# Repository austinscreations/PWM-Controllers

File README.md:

# PWM-Controllers

This project has been expanded - tehre are now controlelrs that use a sheild attached to a LilyGO POE, A board using a D1 mini. both of those baords offer 5ch of LED control

Then theres the PWM controller with 16ch expanble i2c module and the room8266 controlelr for controlling said board.

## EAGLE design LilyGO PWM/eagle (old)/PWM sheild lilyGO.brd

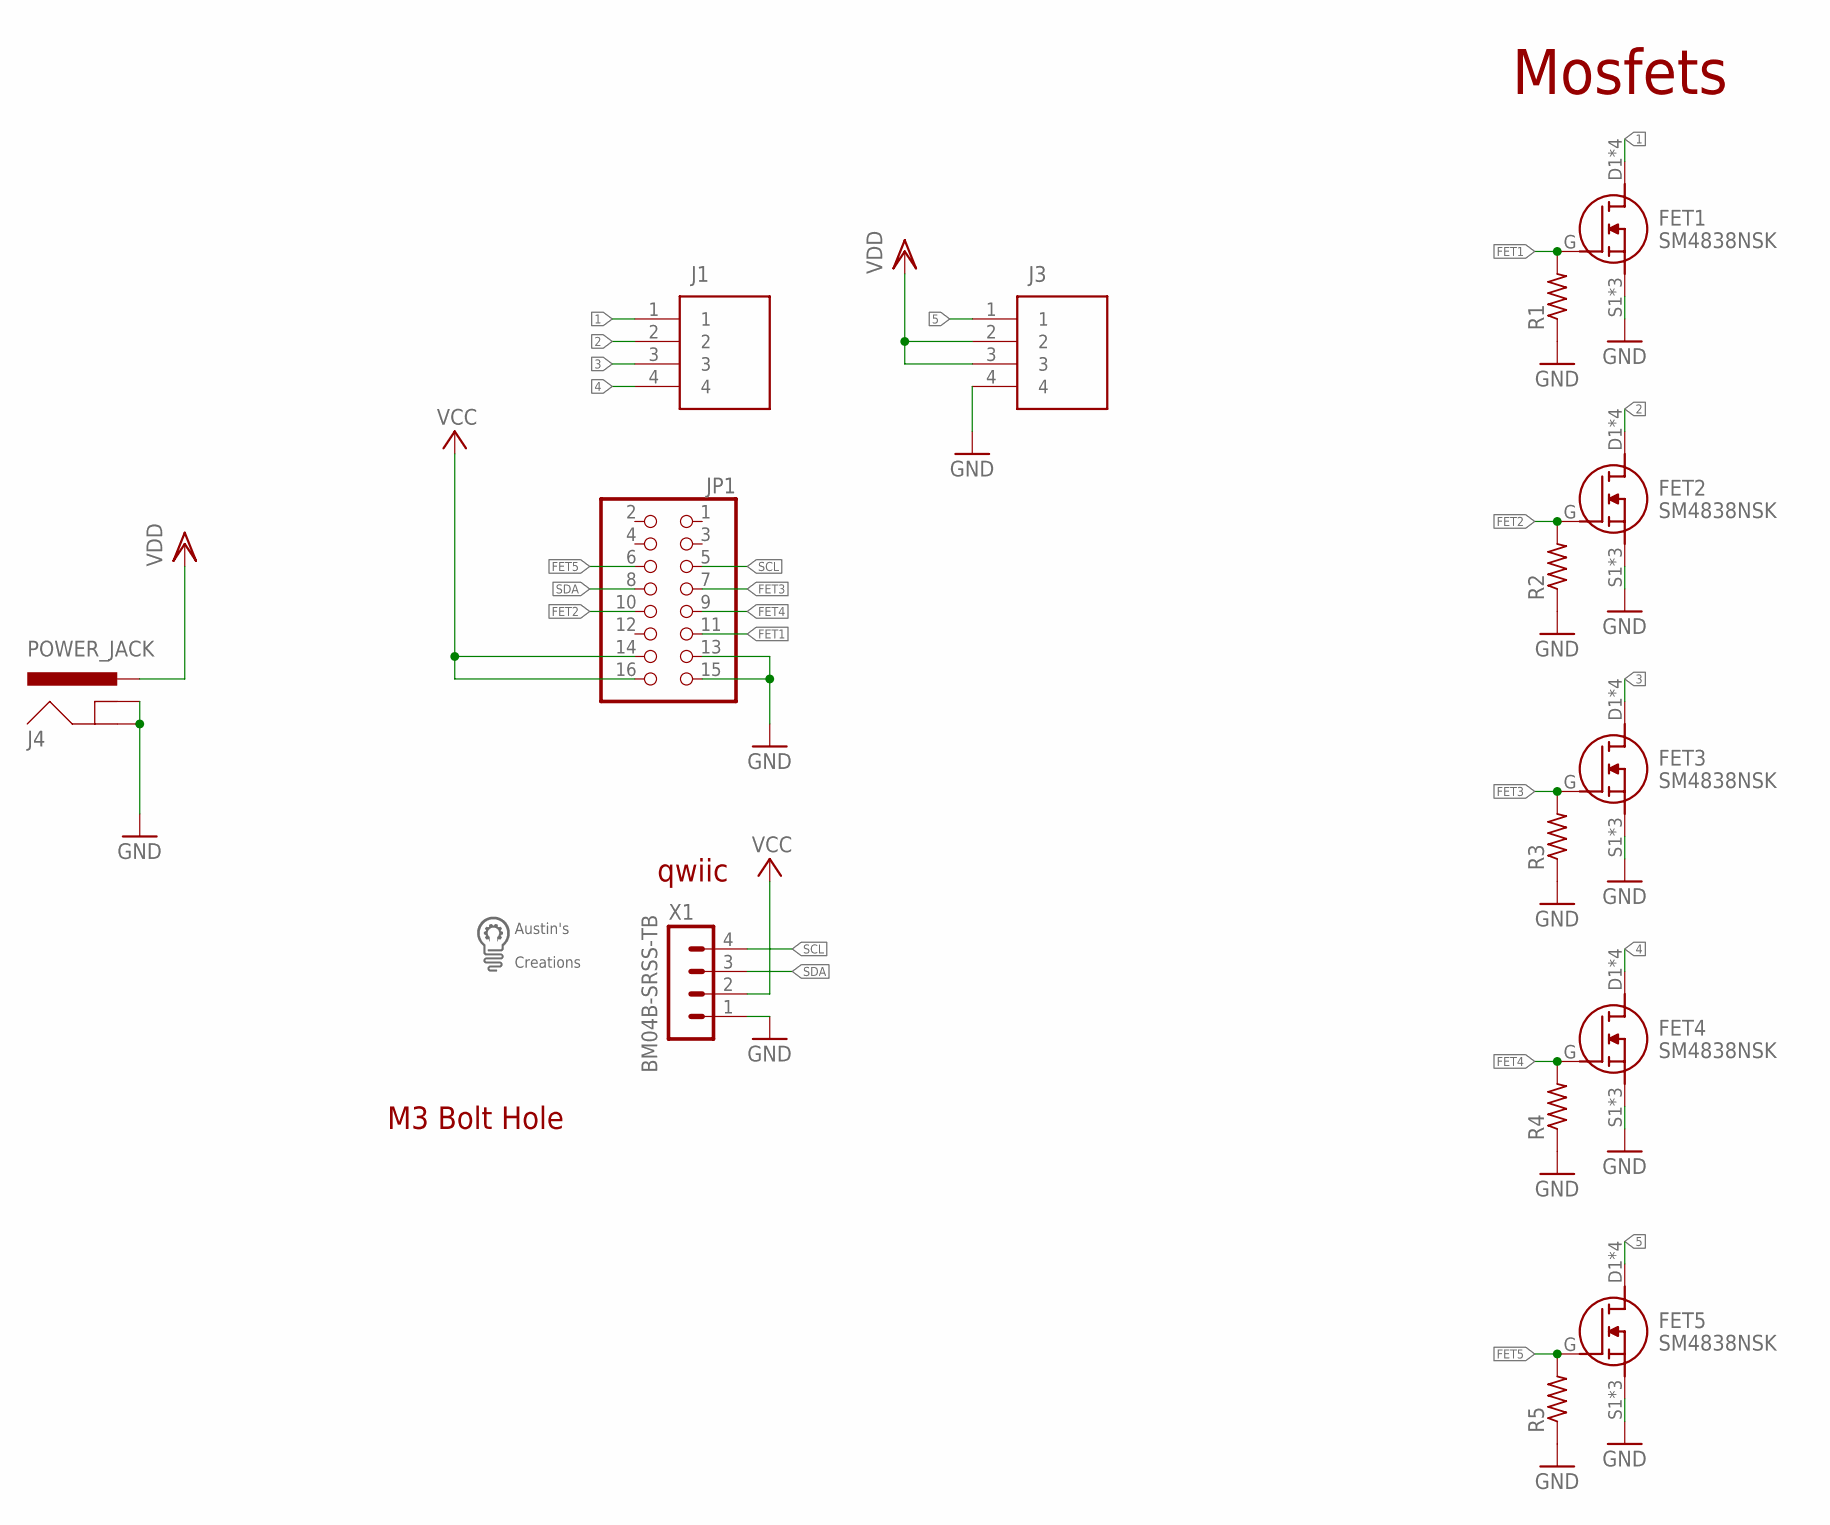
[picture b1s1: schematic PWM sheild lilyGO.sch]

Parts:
FET1, FET2, FET3, FET4, FET5: SM4838NSK
J1, J3: SCREWTERMINAL-4P-5MM
J4: POWER_JACK; POWER_JACK_PTH
JP1: PINHD-2X8; 2X08
R1, R2, R3, R4, R5: R-US_R0603; R0603
U$1: M3BOLTHOLE
U$2: LOGO
X1: BM04B-SRSS-TB

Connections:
1: FET1.D1 (D), FET1.D2 (D), FET1.D3 (D), FET1.D4 (D), J1.1
2: FET2.D1 (D), FET2.D2 (D), FET2.D3 (D), FET2.D4 (D), J1.2
3: FET3.D1 (D), FET3.D2 (D), FET3.D3 (D), FET3.D4 (D), J1.3
4: FET4.D1 (D), FET4.D2 (D), FET4.D3 (D), FET4.D4 (D), J1.4
5: FET5.D1 (D), FET5.D2 (D), FET5.D3 (D), FET5.D4 (D), J3.1
FET1: FET1.G, JP1.11, R1.2
FET2: FET2.G, JP1.10, R2.2
FET3: FET3.G, JP1.7, R3.2
FET4: FET4.G, JP1.9, R4.2
FET5: FET5.G, JP1.6, R5.2
GND: FET1.S1 (S), FET1.S2 (S), FET1.S3 (S), FET2.S1 (S), FET2.S2 (S), FET2.S3 (S), FET3.S1 (S), FET3.S2 (S), FET3.S3 (S), FET4.S1 (S), FET4.S2 (S), FET4.S3 (S), FET5.S1 (S), FET5.S2 (S), FET5.S3 (S), J3.4, J4.GND, J4.GNDBREAK, JP1.13, JP1.15, R1.1, R2.1, R3.1, R4.1, R5.1, X1.1
SCL: JP1.5, X1.4
SDA: JP1.8, X1.3
VCC: JP1.14, JP1.16, X1.2
VDD: J3.2, J3.3, J4.PWR

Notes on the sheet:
Mosfets
qwiic

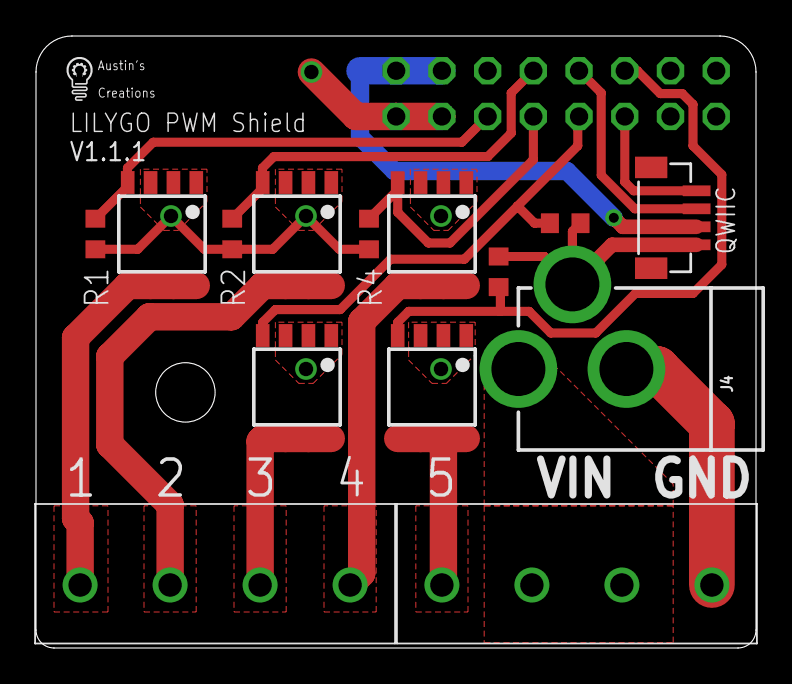
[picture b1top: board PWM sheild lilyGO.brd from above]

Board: 2 copper layers, 40.0 x 34.0 mm, 17 parts (1 on the bottom side), 15 nets.

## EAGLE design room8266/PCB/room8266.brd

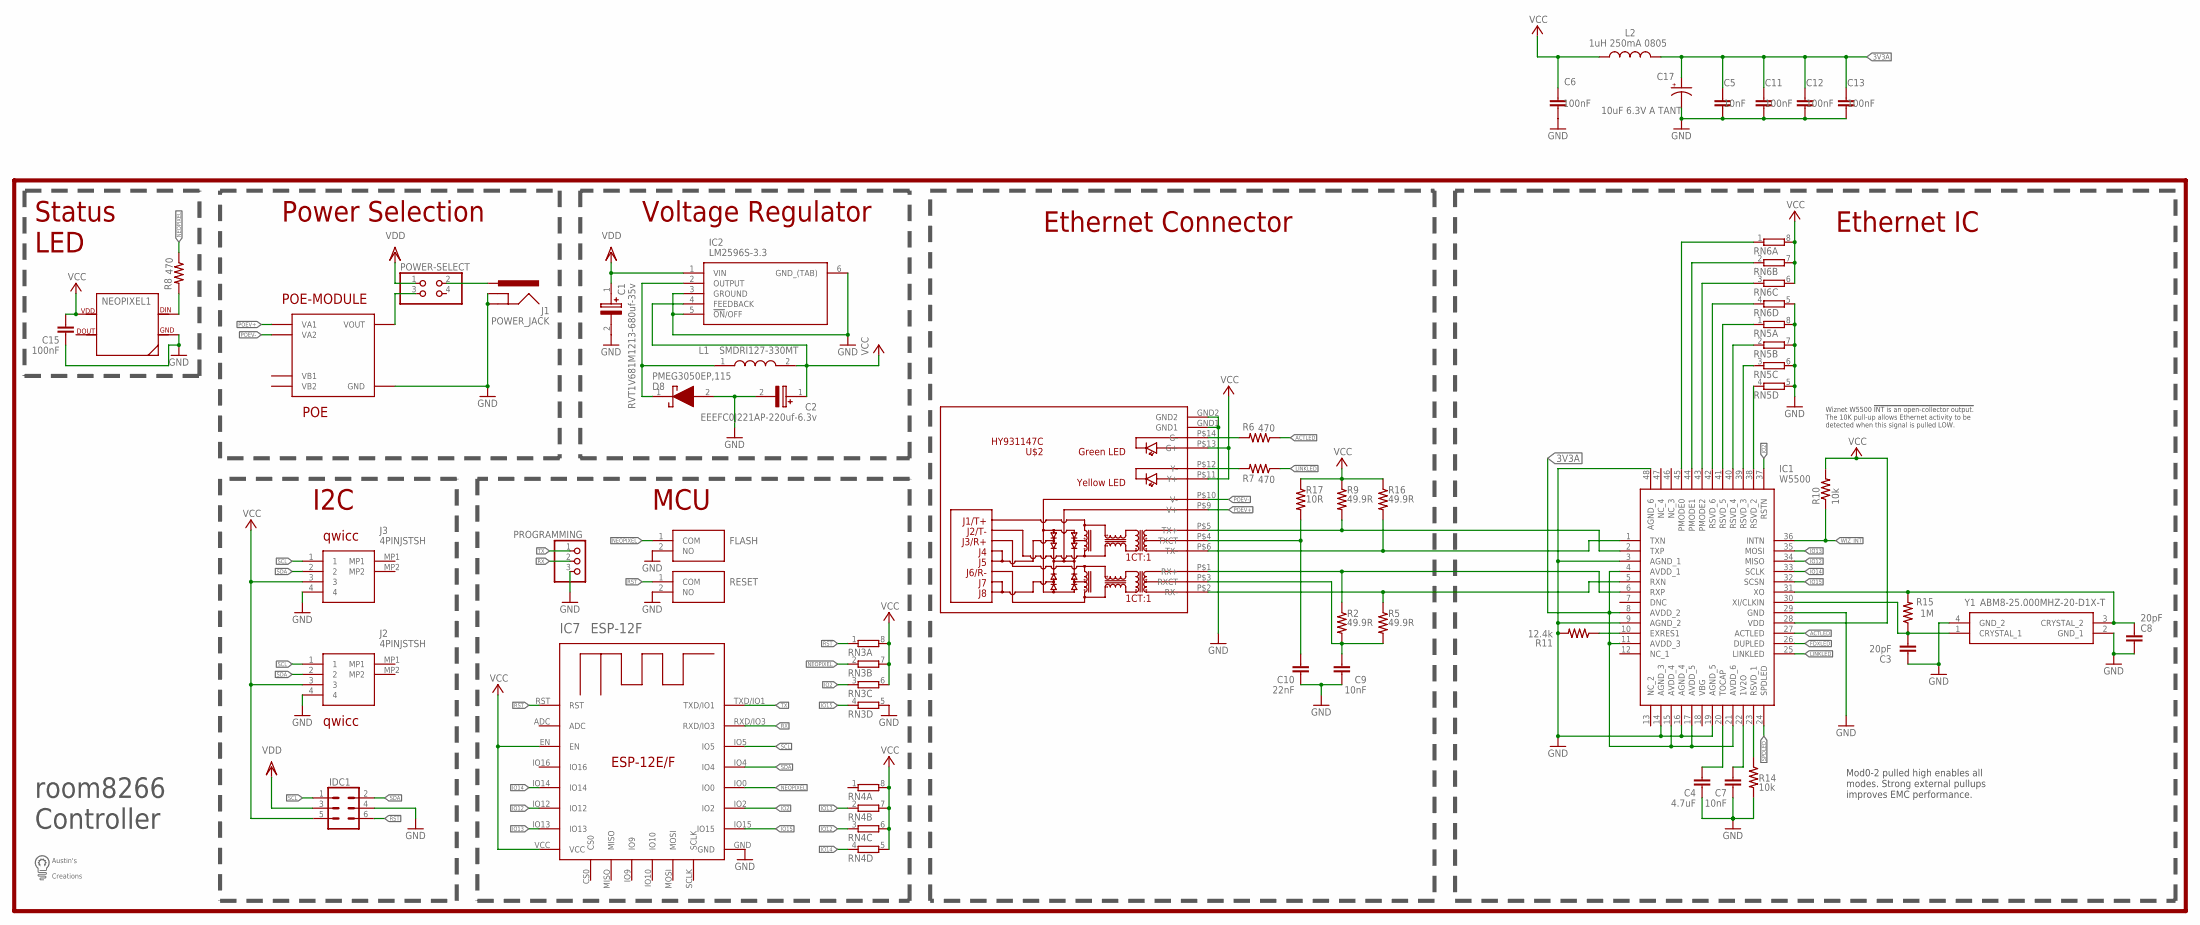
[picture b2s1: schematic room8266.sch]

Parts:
C1: RVT1V681M1213-680uf-35v; CAPAE1350X1400N
C2: EEEFC0J221AP-220uf-6.3v; CAPAE830X650N
C3, C8: 20pF; C0603
C4: 4.7uF; C0603
C5, C7, C9: 10nF; C0603
C6, C11, C12, C13, C15: 100nF; C0603
C10: 22nF; C0603
C17: 10uF 6.3V A TANT; A/3216-18W
D8: PMEG3050EP,115; PMEG3050EP115
FLASH: PTS636_SM25F_SMTR_LFS; PTS636SM25FSMTRLFS
IC1: W5500; QFP50P900X900X160-48N
IC2: LM2596S-3.3; TO170P1435X465-6N
IC7: ESP-12F; ESP-12E
IDC1: CONN_03X2SHROUD; 2X3-SHROUDED
J1: POWER_JACK; POWER_JACK_PTH
J2, J3: 4PINJSTSH; 665104131822
L1: SMDRI127-330MT; INDPM120120X800N
L2: 1uH 250mA 0805; L2012C
NEOPIXEL1: SK6812NEOPIXEL5050; SK6812
POE-MODULE: POE; DP1435
POWER-SELECT: PINHD-2X2; 2X02
PROGRAMMING: PINHD-1X3; 1X03
R2, R5, R9, R16: 49.9R; R0603
R6, R7, R8: 470; R0603
R10, R14: 10k; R0603
R11: 12.4k; R0603
R15: 1M; R0603
R17: 10R; R0603
RESET: PTS636_SM25F_SMTR_LFS; PTS636SM25FSMTRLFS
RN3, RN4, RN5, RN6: 4R-N0603-ARC; 0603-ARC
U$1: LOGOMED
U$2: HY931147C
Y1: ABM8-25.000MHZ-20-D1X-T; ABM825000MHZ10B1UT

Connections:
3V3A: C5.1, C11.1, C12.1, C13.1, C17.+, IC1.4 (AVDD_1), IC1.8 (AVDD_2), IC1.11 (AVDD_3), IC1.15 (AVDD_4), IC1.17 (AVDD_5), IC1.21 (AVDD_6), L2.2
ACTLED: IC1.27 (ACTLED), R6.1
FDXLED: IC1.26 (DUPLED)
GND: C1.2 (-), C2.2 (-), C3.1, C4.1, C5.2, C6.2, C7.1, C8.1, C9.1, C10.1, C11.2, C12.2, C13.2, C15.1, C17.-, D8.2 (A), FLASH.2 (NO), IC1.3 (AGND_1), IC1.9 (AGND_2), IC1.14 (AGND_3), IC1.16 (AGND_4), IC1.19 (AGND_5), IC1.29 (GND), IC1.48 (AGND_6), IC2.3 (GROUND), IC2.5 (!ON!/OFF), IC2.6 (GND_(TAB)), IC7.GND, IDC1.4, J1.GND, J1.GNDBREAK, J2.4, J3.4, NEOPIXEL1.3 (GND), POE-MODULE.GND, PROGRAMMING.3, R11.2, R14.2, RESET.2 (NO), RN3.5 (2), RN5.5 (2), RN5.6 (2), RN5.7 (2), RN5.8 (2), RN6.5 (2), U$2.GND1, U$2.GND2, Y1.2 (GND_1), Y1.4 (GND_2)
IO2: IC1.37 (RSTN), IC7.IO2, RN3.3 (1)
IO12: IC1.34 (MISO), IC7.IO12, RN4.3 (1)
IO13: IC1.35 (MOSI), IC7.IO13, RN4.2 (1)
IO14: IC1.33 (SCLK), IC7.IO14, RN4.4 (1)
IO15: IC1.32 (SCSN), IC7.IO15, RN3.4 (1)
LINKLED: IC1.25 (LINKLED), R7.1
unnamed: IC1.10 (EXRES1), R11.1
unnamed: IC1.23 (RSVD_1), R14.1
unnamed: IC1.38 (RSVD_2), RN5.4 (1)
unnamed: IC1.39 (RSVD_3), RN5.3 (1)
unnamed: IC1.40 (RSVD_4), RN5.2 (1)
unnamed: IC1.41 (RSVD_5), RN5.1
unnamed: POE-MODULE.VOUT, POWER-SELECT.3
unnamed: IC1.42 (RSVD_6), RN6.4 (1)
unnamed: J1.PWR, POWER-SELECT.2
unnamed: IC1.43 (PMODE2), RN6.3 (1)
unnamed: IC1.44 (PMODE1), RN6.2 (1)
unnamed: IC1.45 (PMODE0), RN6.1
unnamed: C7.2, IC1.22 (1V2O)
unnamed: C3.2, IC1.30 (XI/CLKIN), R15.1, Y1.1 (CRYSTAL_1)
unnamed: C8.2, IC1.31 (XO), R15.2, Y1.3 (CRYSTAL_2)
unnamed: C4.2, IC1.20 (TOCAP)
unnamed: R6.2, U$2.P$14 (G-)
unnamed: D8.1 (K), IC2.2 (OUTPUT), L1.1
unnamed: NEOPIXEL1.4 (DIN), R8.2
unnamed: C10.2, R17.2, U$2.P$4 (TXCT)
unnamed: R7.2, U$2.P$12 (Y-)
unnamed: C9.2, R2.2, R5.2, U$2.P$3 (RXCT)
NEOPIXEL: FLASH.1 (COM), IC7.IO0, R8.1, RN3.2 (1)
POEV+: POE-MODULE.VA1, U$2.P$9 (V+)
POEV-: POE-MODULE.VA2, U$2.P$10 (V-)
RST: IC7.RST, IDC1.6, RESET.1 (COM), RN3.1
RX: IC7.RXD/IO3, PROGRAMMING.2
RXIN: IC1.5 (RXN), R5.1, U$2.P$2 (RX-)
RXIP: IC1.6 (RXP), R2.1, U$2.P$1 (RX+)
SCL: IC7.IO5, IDC1.1, J2.1, J3.1
SDA: IC7.IO4, IDC1.2, J2.2, J3.2
SPDLED: IC1.24 (SPDLED)
TX: IC7.TXD/IO1, PROGRAMMING.1
TXON: IC1.1 (TXN), R16.2, U$2.P$6 (TX-)
TXOP: IC1.2 (TXP), R9.2, U$2.P$5 (TX+)
VCC: C2.1 (+), C6.1, C15.2, IC1.28 (VDD), IC2.4 (FEEDBACK), IC7.EN, IC7.VCC, IDC1.5, J2.3, J3.3, L1.2, L2.1, NEOPIXEL1.1 (VDD), R9.1, R10.2, R16.1, R17.1, RN3.6 (2), RN3.7 (2), RN3.8 (2), RN4.5 (2), RN4.6 (2), RN4.7 (2), RN4.8 (2), RN6.6 (2), RN6.7 (2), RN6.8 (2), U$2.P$11 (Y+), U$2.P$13 (G+)
VDD: C1.1 (+), IC2.1 (VIN), IDC1.3, POWER-SELECT.1
WIZ_INT: IC1.36 (INTN), R10.1

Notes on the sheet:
Mod0-2 pulled high enables all modes. Strong external pullups improves EMC performance.
Wiznet W5500 !INT is an open-collector output. The 10K pull-up allows Ethernet activity to be detected when this signal is pulled LOW.
MCU
qwicc
I2C
Status LED
Power Selection
Voltage Regulator
Ethernet IC
Ethernet Connector
room8266 Controller

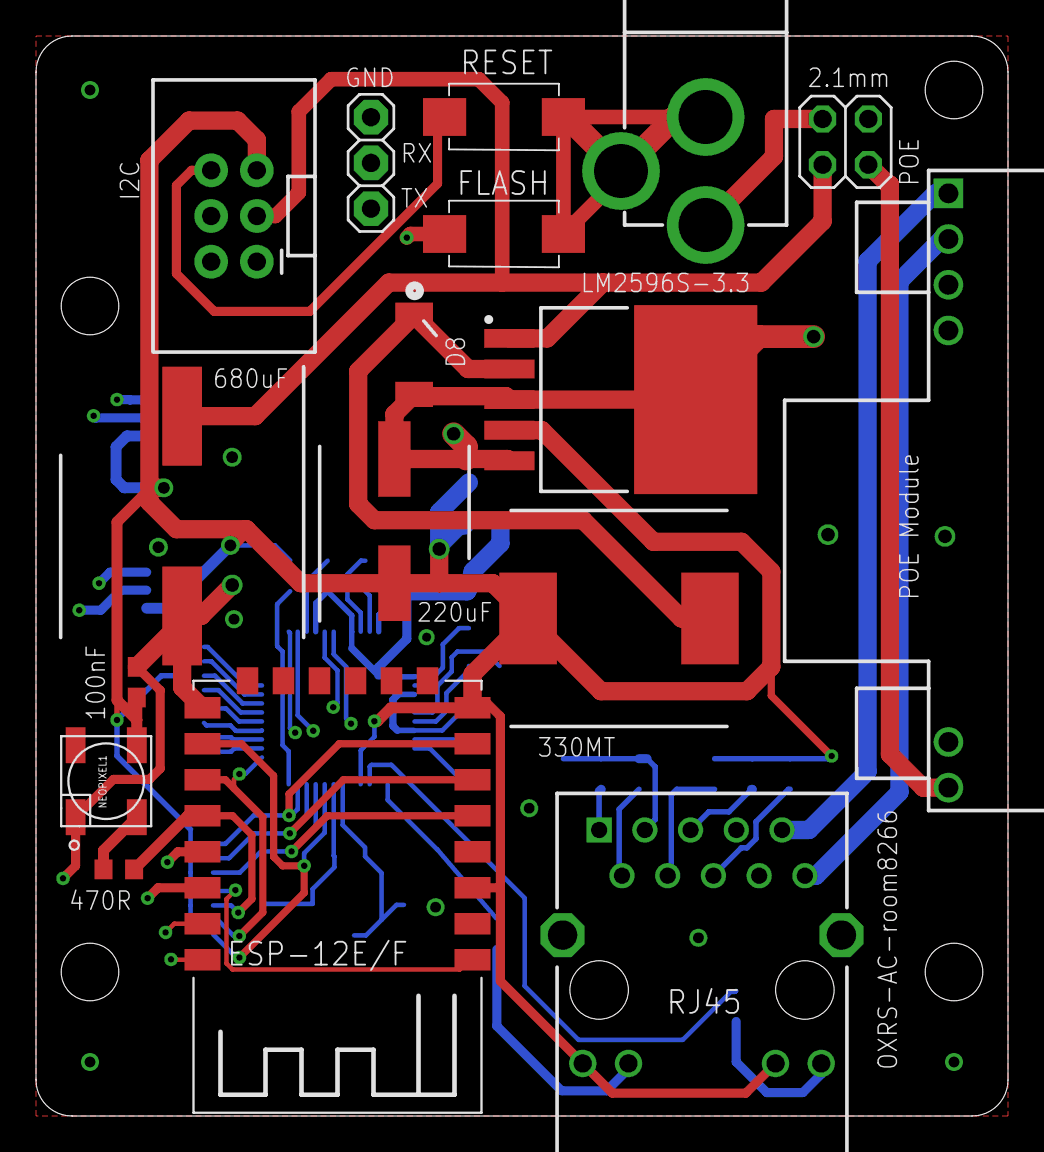
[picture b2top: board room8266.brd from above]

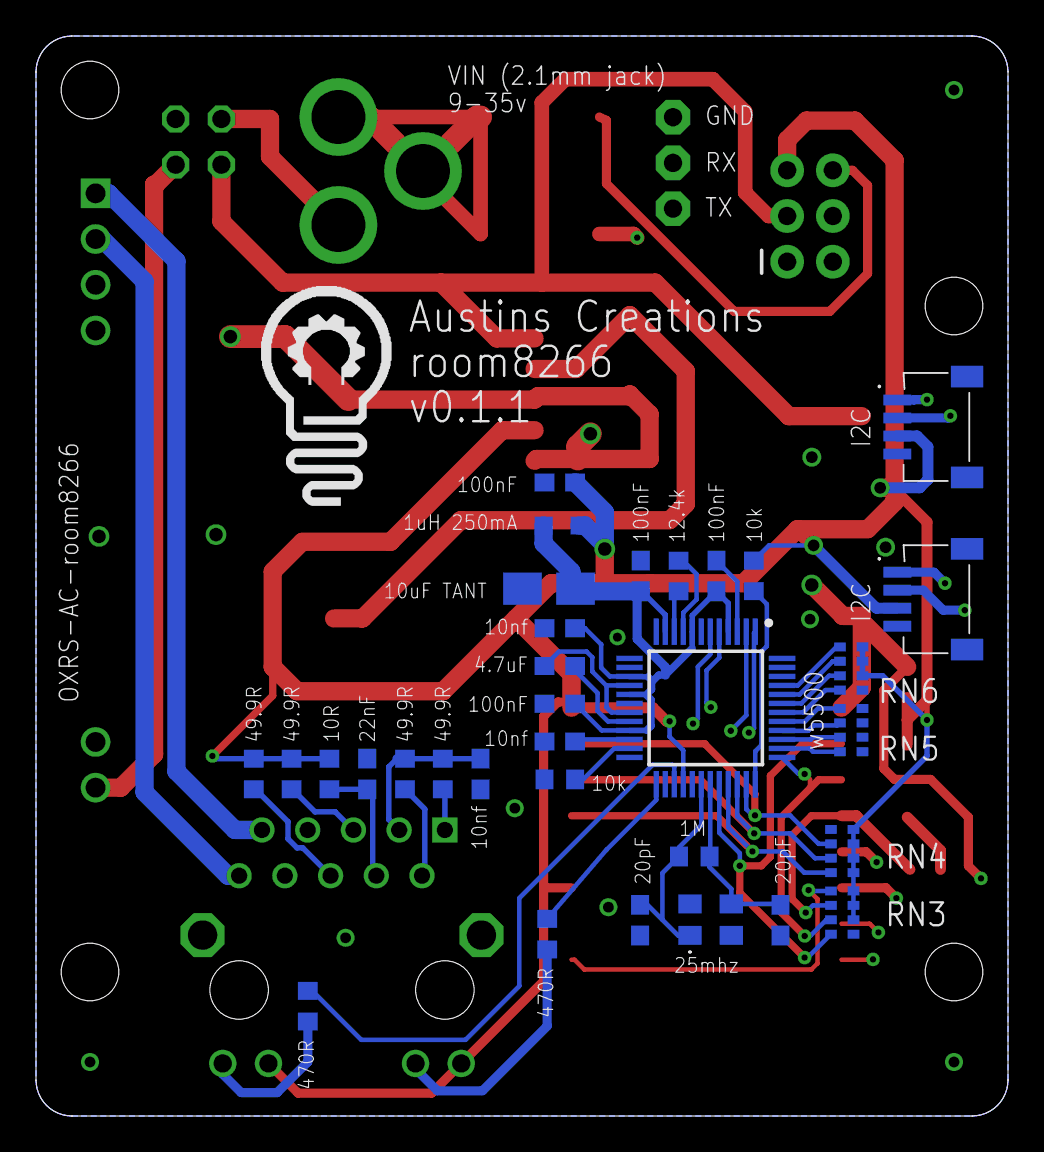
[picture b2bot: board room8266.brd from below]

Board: 4 copper layers, 54.0 x 60.0 mm, 50 parts (33 on the bottom side), 46 nets.

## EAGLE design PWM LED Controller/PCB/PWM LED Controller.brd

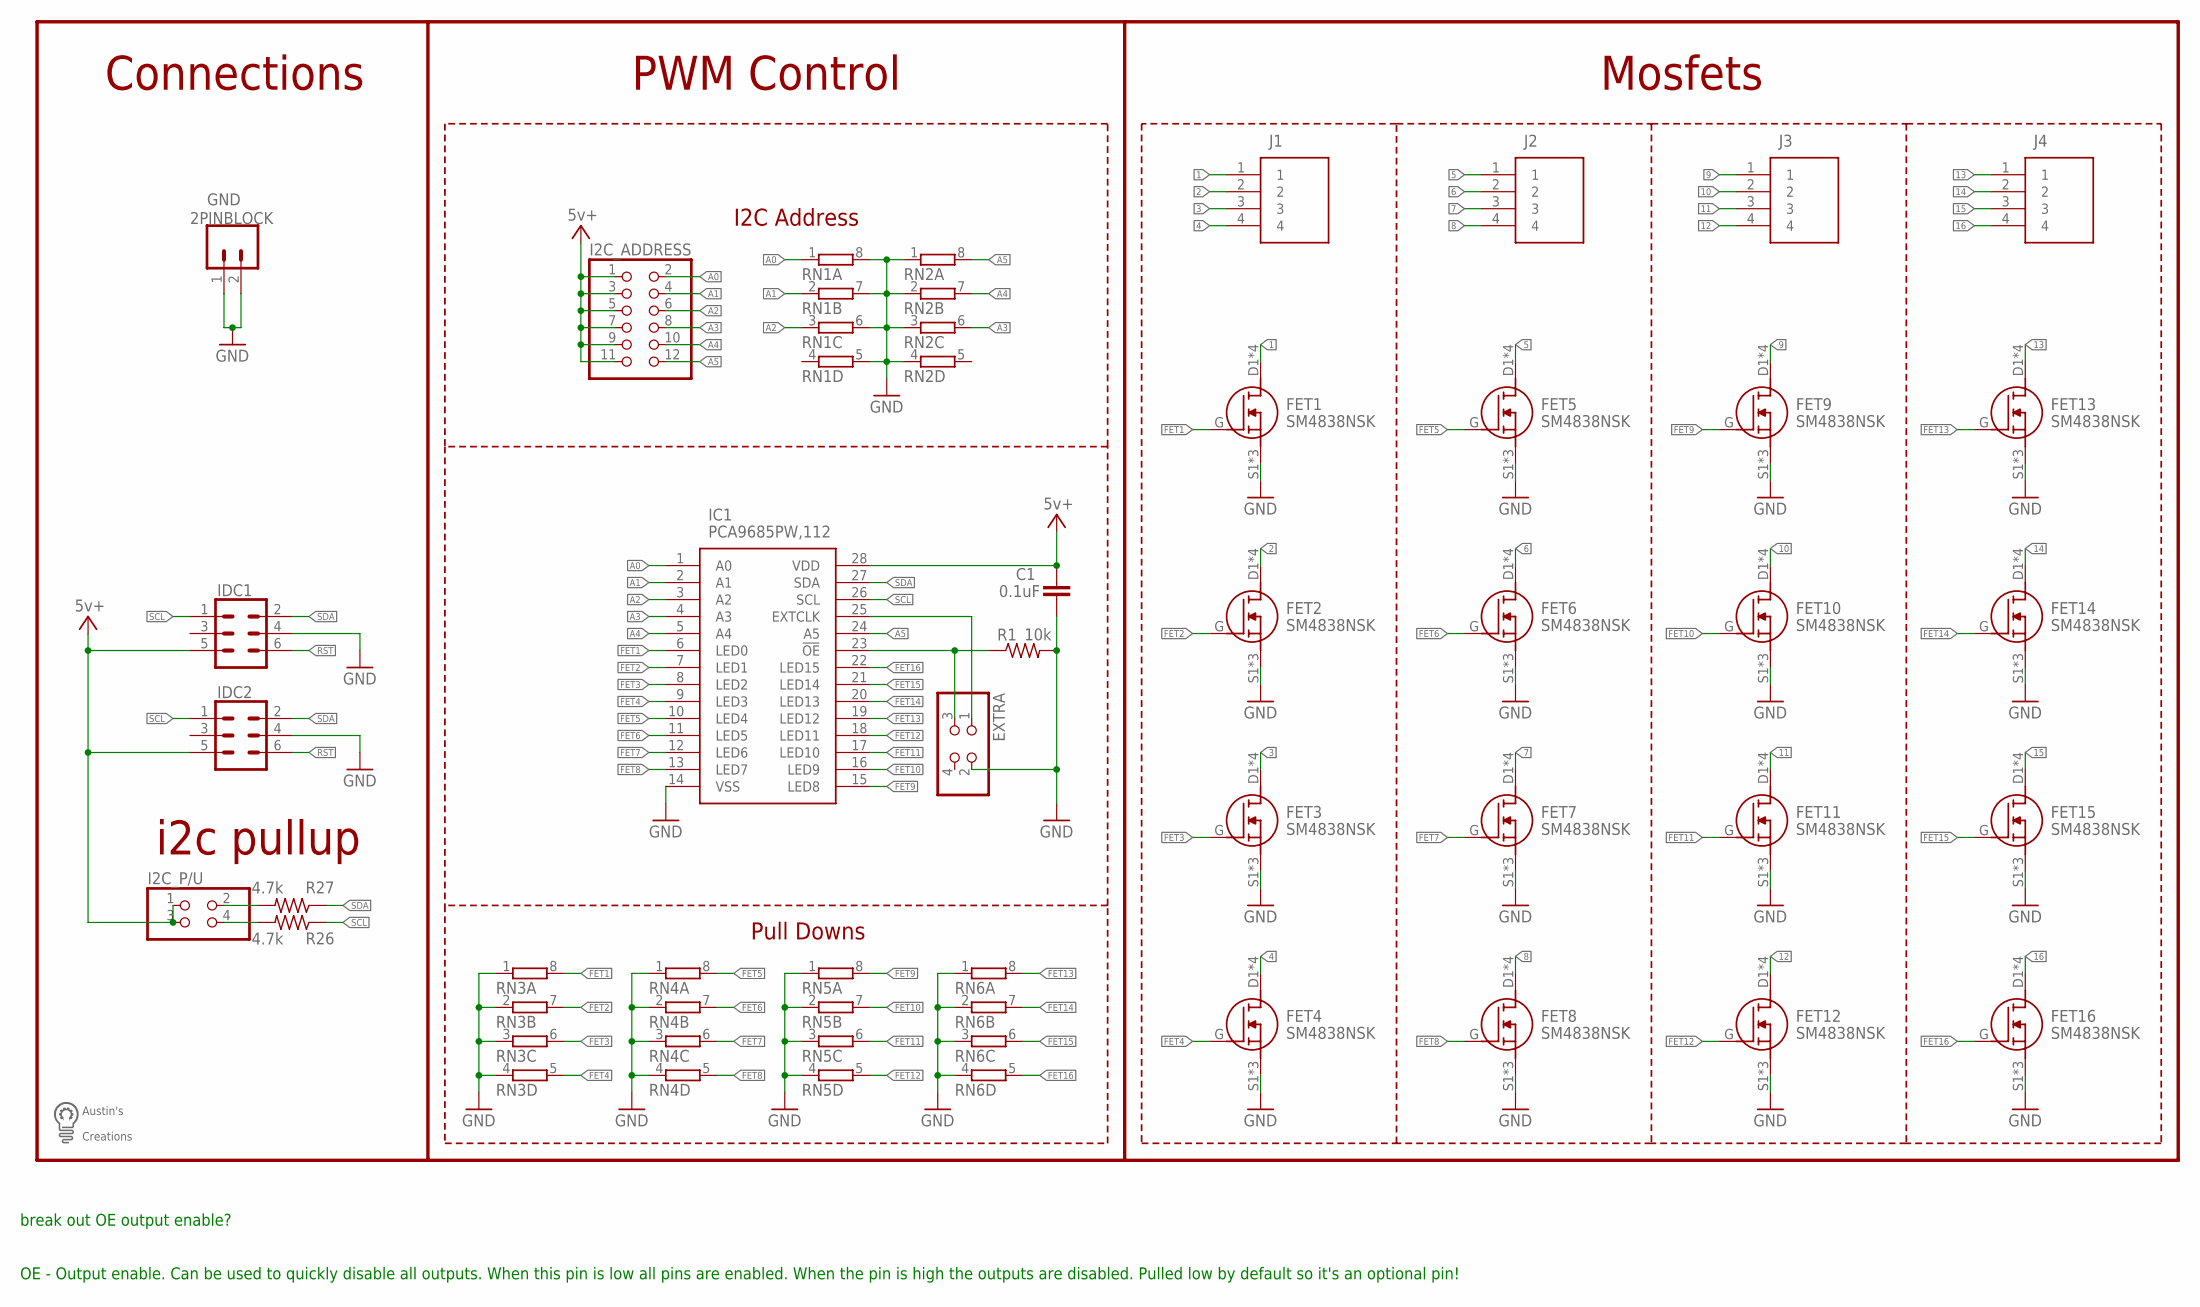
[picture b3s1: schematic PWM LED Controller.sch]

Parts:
C1: 0.1uF; C0603
EXTRA: PINHD-2X2; 2X02
FET1, FET2, FET3, FET4, FET5, FET6, FET7, FET8, FET9, FET10, FET11, FET12, FET13, FET14, FET15, FET16: SM4838NSK
GND: 2PINBLOCK; SCREWTERMINAL-5MM-2
I2C_ADDRESS: PINHD-2X6; 2X06
I2C_P/U: PINHD-2X2; 2X02
IC1: PCA9685PW,112; SOP65P640X110-28N
IDC1, IDC2: CONN_03X2SHROUD; 2X3-SHROUDED
J1, J2, J3, J4: SCREWTERMINAL-4P-5MM
R1: 10k; R0603
R26, R27: 4.7k; R0603
RN1, RN2, RN3, RN4, RN5, RN6: 4R-N0603-ARC; 0603-ARC
U$1: LOGOMED

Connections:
1: FET1.D1 (D), FET1.D2 (D), FET1.D3 (D), FET1.D4 (D), J1.1
2: FET2.D1 (D), FET2.D2 (D), FET2.D3 (D), FET2.D4 (D), J1.2
3: FET3.D1 (D), FET3.D2 (D), FET3.D3 (D), FET3.D4 (D), J1.3
4: FET4.D1 (D), FET4.D2 (D), FET4.D3 (D), FET4.D4 (D), J1.4
5: FET5.D1 (D), FET5.D2 (D), FET5.D3 (D), FET5.D4 (D), J2.1
6: FET6.D1 (D), FET6.D2 (D), FET6.D3 (D), FET6.D4 (D), J2.2
7: FET7.D1 (D), FET7.D2 (D), FET7.D3 (D), FET7.D4 (D), J2.3
8: FET8.D1 (D), FET8.D2 (D), FET8.D3 (D), FET8.D4 (D), J2.4
9: FET9.D1 (D), FET9.D2 (D), FET9.D3 (D), FET9.D4 (D), J3.1
10: FET10.D1 (D), FET10.D2 (D), FET10.D3 (D), FET10.D4 (D), J3.2
11: FET11.D1 (D), FET11.D2 (D), FET11.D3 (D), FET11.D4 (D), J3.3
12: FET12.D1 (D), FET12.D2 (D), FET12.D3 (D), FET12.D4 (D), J3.4
13: FET13.D1 (D), FET13.D2 (D), FET13.D3 (D), FET13.D4 (D), J4.1
14: FET14.D1 (D), FET14.D2 (D), FET14.D3 (D), FET14.D4 (D), J4.2
15: FET15.D1 (D), FET15.D2 (D), FET15.D3 (D), FET15.D4 (D), J4.3
16: FET16.D1 (D), FET16.D2 (D), FET16.D3 (D), FET16.D4 (D), J4.4
A0: I2C_ADDRESS.2, IC1.1 (A0), RN1.1
A1: I2C_ADDRESS.4, IC1.2 (A1), RN1.2 (1)
A2: I2C_ADDRESS.6, IC1.3 (A2), RN1.3 (1)
A3: I2C_ADDRESS.8, IC1.4 (A3), RN2.6 (2)
A4: I2C_ADDRESS.10, IC1.5 (A4), RN2.7 (2)
A5: I2C_ADDRESS.12, IC1.24 (A5), RN2.8 (2)
FET1: FET1.G, IC1.6 (LED0), RN3.8 (2)
FET2: FET2.G, IC1.7 (LED1), RN3.7 (2)
FET3: FET3.G, IC1.8 (LED2), RN3.6 (2)
FET4: FET4.G, IC1.9 (LED3), RN3.5 (2)
FET5: FET5.G, IC1.10 (LED4), RN4.8 (2)
FET6: FET6.G, IC1.11 (LED5), RN4.7 (2)
FET7: FET7.G, IC1.12 (LED6), RN4.6 (2)
FET8: FET8.G, IC1.13 (LED7), RN4.5 (2)
FET9: FET9.G, IC1.15 (LED8), RN5.8 (2)
FET10: FET10.G, IC1.16 (LED9), RN5.7 (2)
FET11: FET11.G, IC1.17 (LED10), RN5.6 (2)
FET12: FET12.G, IC1.18 (LED11), RN5.5 (2)
FET13: FET13.G, IC1.19 (LED12), RN6.8 (2)
FET14: FET14.G, IC1.20 (LED13), RN6.7 (2)
FET15: FET15.G, IC1.21 (LED14), RN6.6 (2)
FET16: FET16.G, IC1.22 (LED15), RN6.5 (2)
GND: C1.2, EXTRA.2, FET1.S1 (S), FET1.S2 (S), FET1.S3 (S), FET2.S1 (S), FET2.S2 (S), FET2.S3 (S), FET3.S1 (S), FET3.S2 (S), FET3.S3 (S), FET4.S1 (S), FET4.S2 (S), FET4.S3 (S), FET5.S1 (S), FET5.S2 (S), FET5.S3 (S), FET6.S1 (S), FET6.S2 (S), FET6.S3 (S), FET7.S1 (S), FET7.S2 (S), FET7.S3 (S), FET8.S1 (S), FET8.S2 (S), FET8.S3 (S), FET9.S1 (S), FET9.S2 (S), FET9.S3 (S), FET10.S1 (S), FET10.S2 (S), FET10.S3 (S), FET11.S1 (S), FET11.S2 (S), FET11.S3 (S), FET12.S1 (S), FET12.S2 (S), FET12.S3 (S), FET13.S1 (S), FET13.S2 (S), FET13.S3 (S), FET14.S1 (S), FET14.S2 (S), FET14.S3 (S), FET15.S1 (S), FET15.S2 (S), FET15.S3 (S), FET16.S1 (S), FET16.S2 (S), FET16.S3 (S), GND.1, GND.2, IC1.14 (VSS), IDC1.4, IDC2.4, R1.2, RN1.5 (2), RN1.6 (2), RN1.7 (2), RN1.8 (2), RN2.1, RN2.2 (1), RN2.3 (1), RN2.4 (1), RN3.1, RN3.2 (1), RN3.3 (1), RN3.4 (1), RN4.1, RN4.2 (1), RN4.3 (1), RN4.4 (1), RN5.1, RN5.2 (1), RN5.3 (1), RN5.4 (1), RN6.1, RN6.2 (1), RN6.3 (1), RN6.4 (1)
unnamed: I2C_P/U.4, R26.2
unnamed: I2C_P/U.2, R27.2
unnamed: EXTRA.1, IC1.25 (EXTCLK)
unnamed: EXTRA.3, IC1.23 (!OE), R1.1
RST: IDC1.6, IDC2.6
SCL: IC1.26 (SCL), IDC1.1, IDC2.1, R26.1
SDA: IC1.27 (SDA), IDC1.2, IDC2.2, R27.1
VCC: C1.1, I2C_ADDRESS.1, I2C_ADDRESS.3, I2C_ADDRESS.5, I2C_ADDRESS.7, I2C_ADDRESS.9, I2C_ADDRESS.11, I2C_P/U.1, I2C_P/U.3, IC1.28 (VDD), IDC1.5, IDC2.5

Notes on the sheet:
i2c pullup
Mosfets
Pull Downs
I2C Address
PWM Control
Connections
break out OE output enable? OE - Output enable. Can be used to quickly disable all outputs. When this pin is low all pins are enabled. When the pin is high the outputs are disabled. Pulled low by default so it's an optional pin!

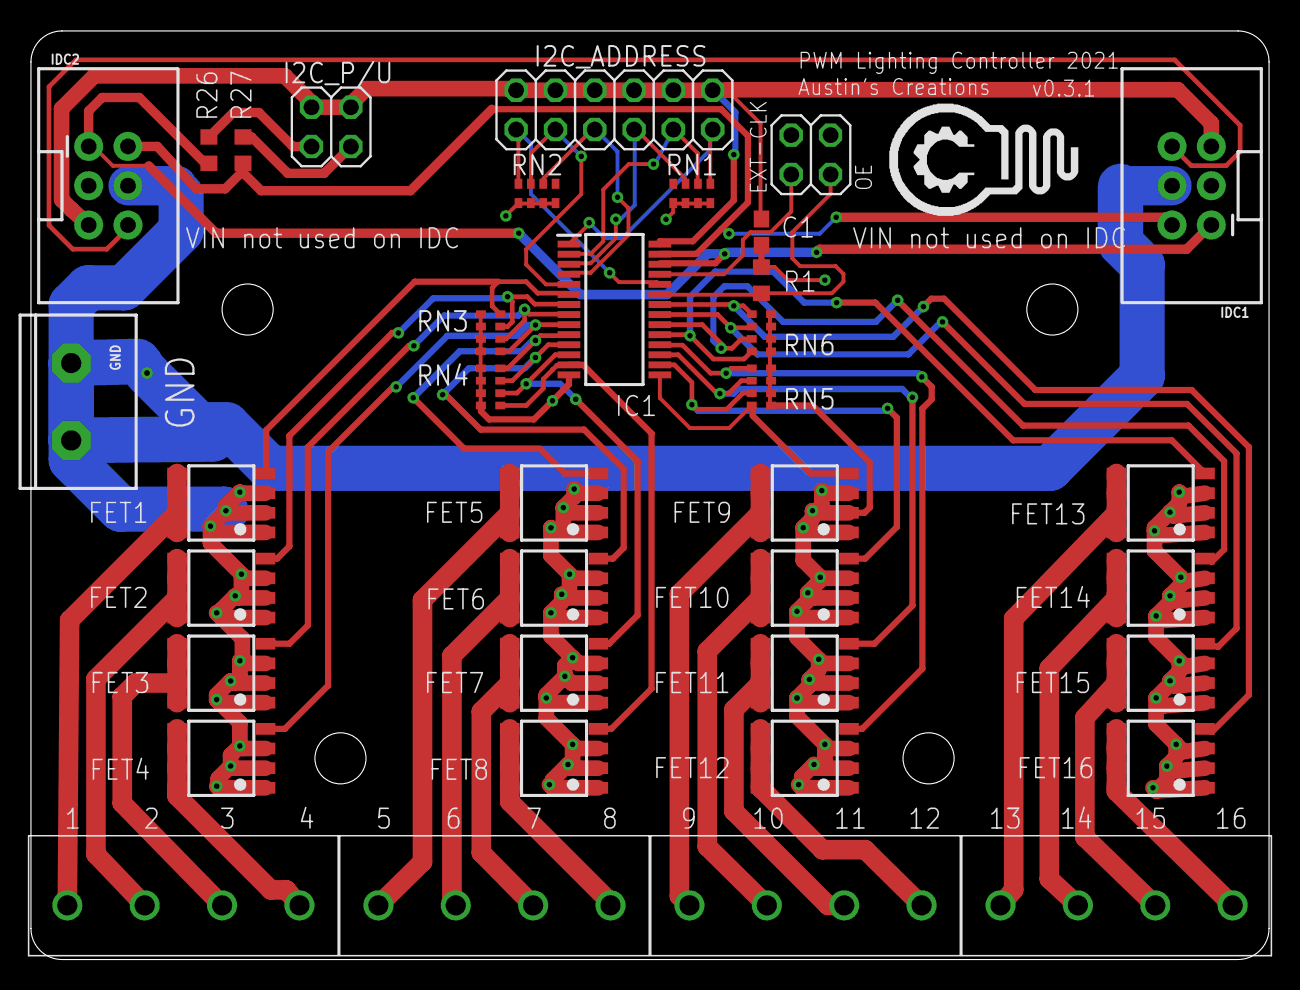
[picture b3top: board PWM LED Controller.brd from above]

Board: 2 copper layers, 80.0 x 60.0 mm, 38 parts (0 on the bottom side), 47 nets.

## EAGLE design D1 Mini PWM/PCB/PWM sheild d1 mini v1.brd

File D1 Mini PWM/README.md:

Placeholder

newest version is done in kicad - switched from using the D1 mini to using the esp-12f directly along with adding usb c programming and debugging support

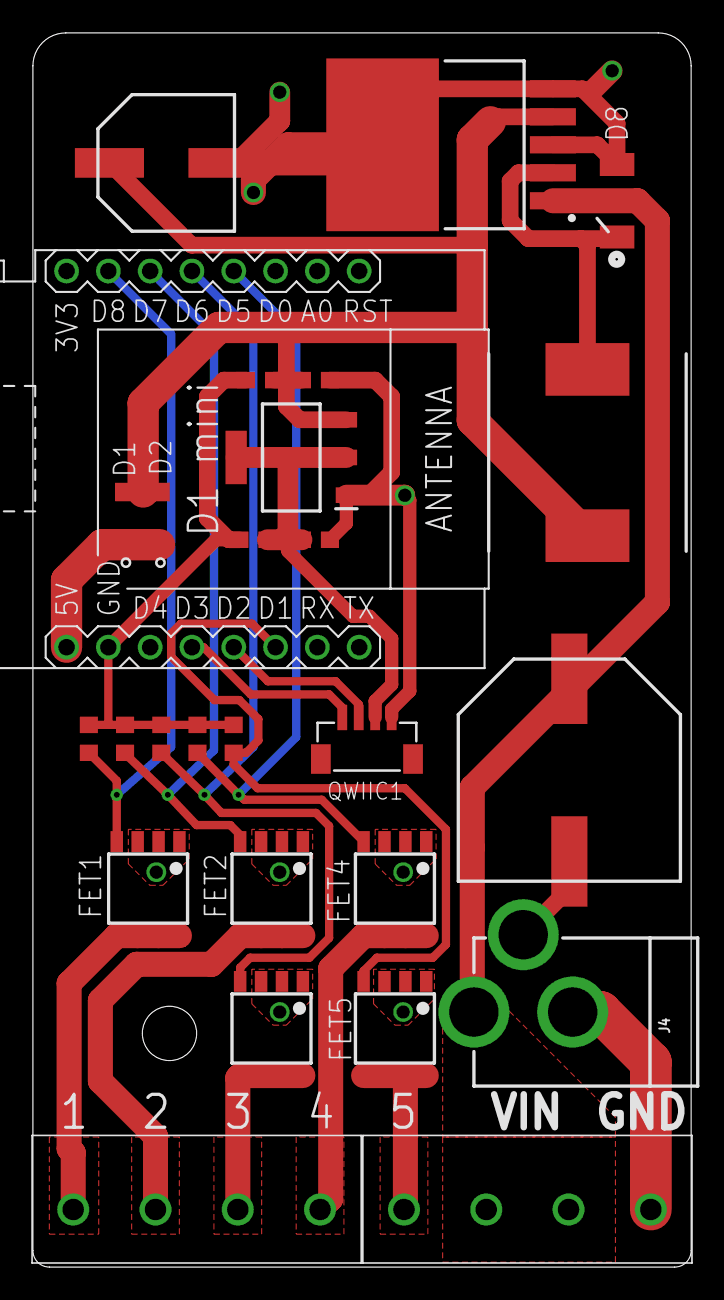
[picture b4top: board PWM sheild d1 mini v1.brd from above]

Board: 2 copper layers, 40.0 x 75.0 mm, 29 parts (1 on the bottom side), 18 nets.

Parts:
C1, C3: 100nf; C0603
C2, C4: 10uf; C0603
C5: RVT1V681M1213-680uf-35v; CAPAE1350X1400N
C6: EEEFC0J221AP-220uf-6.3v; CAPAE830X650N
D1, D2: SM4007PL; SODFL3718X125N
D8: PMEG3050EP,115; PMEG3050EP115
FET1, FET2, FET3, FET4, FET5: SM4838NSK
IC1: AMS1117-3.3V; SOT229P700X180-4N
IC2: LM2596S-5.0; TO170P1435X465-6N
J1, J3: SCREWTERMINAL-4P-5MM
J4: POWER_JACK; POWER_JACK_PTH
L1: SMDRI127-330MT; INDPM120120X800N
QWIIC1: QWIICUPRIGHT; BM04B-SRSS-TB
R1, R2, R3, R4, R5: R0603
U$1: M3BOLTHOLE
U$3: WEMOS-D1-MINI
U$4: LOGOMED

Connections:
1: FET1.D1, FET1.D2, FET1.D3, FET1.D4, J1.1
2: FET2.D1, FET2.D2, FET2.D3, FET2.D4, J1.2
3: FET3.D1, FET3.D2, FET3.D3, FET3.D4, J1.3
3.3V: C3.2, C4.2, IC1.2, IC1.4, QWIIC1.2
4: FET4.D1, FET4.D2, FET4.D3, FET4.D4, J1.4
5: FET5.D1, FET5.D2, FET5.D3, FET5.D4, J3.1
FET1: FET1.G, R1.2, U$3.JP1.7
FET2: FET2.G, R2.2, U$3.JP1.6
FET3: FET3.G, R3.2, U$3.JP1.5
FET4: FET4.G, R4.2, U$3.JP1.4
FET5: FET5.G, R5.2, U$3.JP2.3
GND: C1.2, C2.2, C3.1, C4.1, C5.2, C6.2, D8.2, FET1.S1, FET1.S2, FET1.S3, FET2.S1, FET2.S2, FET2.S3, FET3.S1, FET3.S2, FET3.S3, FET4.S1, FET4.S2, FET4.S3, FET5.S1, FET5.S2, FET5.S3, IC1.1, IC2.3, IC2.5, IC2.6, J3.4, J4.GND, J4.GNDBREAK, QWIIC1.1, R1.1, R2.1, R3.1, R4.1, R5.1, U$3.JP2.7
unnamed: D1.1, D2.1, U$3.JP2.8
unnamed: D8.1, IC2.2, L1.1
SCL: QWIIC1.4, U$3.JP2.5
SDA: QWIIC1.3, U$3.JP2.4
VCC: C1.1, C2.1, C6.1, D1.2, D2.2, IC1.3, IC2.4, L1.2
VDD: C5.1, IC2.1, J3.2, J3.3, J4.PWR

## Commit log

2021-08-06 Create LICENSE
2021-08-06 Add files via upload
    added missing vertical measurements for holes
2021-08-13 Add files via upload
    adding code
2021-08-13 Update README.md
    add video demo link
2021-09-16 updating example flow
    updated the example flow to use less mqtt nodes to make setup easier.
2021-10-14 Add files via upload
    adding 3d printable cases
    this holds both the PWM controller and the room8266 controller
2022-01-25 project scope increase
2022-01-25 Rename readme.md to README.md
2022-01-25 Create 3D Printable Cases
2022-01-26 updating stub tolerance for mating with lid
2022-12-27 no longer relevant

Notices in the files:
parts and their libraries:
diy-modules: Released under the Creative Commons Attribution 4.0 International License: http://creativecommons.org/licenses/by/4.0
